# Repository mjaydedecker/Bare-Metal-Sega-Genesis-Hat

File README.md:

# Sega Genesis Controller HAT

A passive Raspberry Pi HAT exposing two DB9 (DE-9) ports for original Sega
Genesis / Mega Drive controllers, wired directly to the Pi's 40-pin GPIO
header.

Licensed under [CERN-OHL-S v2](LICENSE) — see [License](#license) below.

This board has no firmware of its own. The pin assignment and electrical
contract it implements are owned by the firmware repo,
[Bare-Metal-Sega-Genesis](../Bare-Metal-Sega-Genesis), specifically
`src/input/sega_board.h` and
`docs/superpowers/specs/2026-06-25-gpio-sega-controllers-design.md`. If
those ever disagree with this repo, the firmware repo wins — update this
board to match it, not the other way around.

See `docs/superpowers/specs/2026-07-21-controller-hat-v1-design.md` for the
full design rationale (why no ID EEPROM, no protection circuitry, no
stacking header) and `docs/superpowers/plans/2026-07-21-controller-hat-v1.md`
for how it was built.

A GitHub Actions workflow (`.github/workflows/verify-pinmap.yml`) checks on
every push that this board's schematic wiring matches the firmware repo's
`sega_board.h` exactly.

## Files

- `genesis-controller-hat.kicad_pro` / `.kicad_sch` / `.kicad_pcb` — the
  KiCad 10 project.
- `design_files/` — source design assets (currently the Bare-Metal Genesis
  logo handoff package); not needed to open or modify the board, kept for
  provenance.
- `scripts/` — the editing scripts used to build the schematic and PCB from
  KiCad's official `RaspberryPi-HAT` template. Not needed to open or modify
  the board in the KiCad GUI; kept for provenance/audit.

## Verifying the board

```bash
kicad-cli sch erc --severity-all genesis-controller-hat.kicad_sch
kicad-cli pcb drc --severity-all genesis-controller-hat.kicad_pcb
python3 scripts/check_pinmap.py ../Bare-Metal-Sega-Genesis/src/input/sega_board.h
```

`check_pinmap.py` (also run in CI on every push) confirms the schematic's
actual wiring matches the firmware repo's `sega_board.h`.

## License

Licensed under the [CERN Open Hardware Licence Version 2 - Strongly
Reciprocal (CERN-OHL-S v2)](LICENSE). Anyone may use, study, modify, and
distribute this design, including commercially — derivatives that are
distributed (as hardware or as design files) must be released under the
same license, with source design files made available. See the
[CERN-OHL-S FAQ](https://ohwr.org/project/cernohl/wikis/faq) for a plain-
language summary; the `LICENSE` file is the authoritative text.

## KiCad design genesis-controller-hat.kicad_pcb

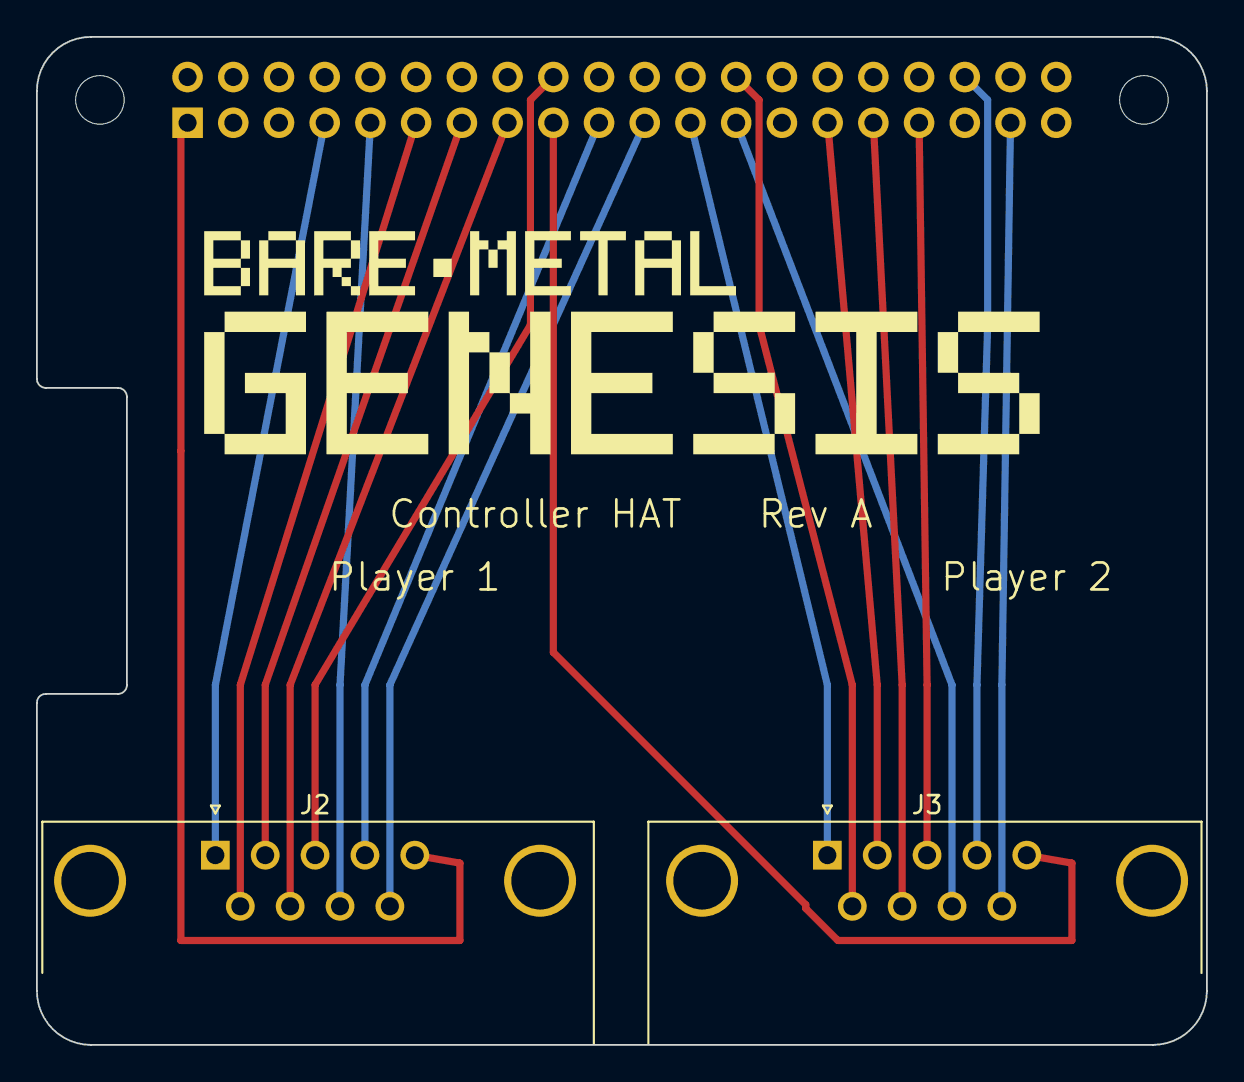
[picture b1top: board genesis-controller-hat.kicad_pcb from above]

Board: 2 copper layers, 65.0 x 56.0 mm, 5 parts (1 on the bottom side), 16 nets.

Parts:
J1: PinSocket_2x20_P2.54mm_Vertical
J2, J3: DSUB-9_Pins_Horizontal_P2.77x2.84mm_EdgePinOffset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; DSUB-9_Pins_Horizontal_P2.77x2.84mm_EdgePinOffset7.70mm_Hou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
MH1, MH2: MountingHole_2.7mm_M2.5

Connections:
+3V3: J1.1, J1.17, J2.5, J3.5
/GPIO4/GPCLK0: J1.7, J2.1
/GPIO5: J1.29, J3.2
/GPIO6: J1.31, J3.7
/GPIO7/SPI0.CE1: J1.26, J3.6
/GPIO9/SPI0.MISO: J1.21, J2.9
/GPIO10/SPI0.MOSI: J1.19, J2.4
/GPIO11/SPI0.SCLK: J1.23, J3.1
/GPIO13/PWM1: J1.33, J3.3
/GPIO16: J1.36, J3.4
/GPIO17: J1.11, J2.6
/GPIO22: J1.15, J2.7
/GPIO24: J1.18, J2.3
/GPIO26: J1.37, J3.9
/GPIO27: J1.13, J2.2
GND: J1.6, J1.9, J1.14, J1.20, J1.25, J1.30, J1.34, J1.39, J2.8, J3.8
